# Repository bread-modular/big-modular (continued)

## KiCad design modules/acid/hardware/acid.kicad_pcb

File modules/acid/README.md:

# ACID: MIDI oscillator + envelope + vactrol SVF (10HP)

Bread Modular **MCO** + **ENV** (one ATtiny1616) and **SVF** (two-vactrol state-variable
filter, LP / HP / BP outs) on one Eurorack module, at Bread Modular's 3.3 V signal level. Each
output is one TL072 stage with a gain solder jumper on the back: x3 (shipped, the LOW level),
x3.9, or x11.1 (the user's BM DRIVE at 75 %).

| Panel (top to bottom) | Circuit |
|---|---|
| **MIDI** in, **AUDIO** in, **CV** in (top row) | MIDI: 8bit / LOW NPN front end, JP1 protected/direct jumper. Bypasses: AUDIO 10 Vpp -> 0..3.3 V (clips), unpatched = MCO; CV 0..5 V -> 0..3.3 V, unpatched = envelope |
| **DETUNE**, **MIX** | BM MCO knobs |
| **ATTACK**, **RELEASE** | BM ENV time knobs (attack = hold in HR mode), 4 mm lower than DETUNE / MIX |
| **HR / AR / ASR** LEDs, **MODE** button | Envelope model select (BM ENV algorithms) |
| **REC** button + LED (LED right of the button) | Records the envelope knob positions |
| **FREQ** | BM SVF cutoff/CV amount |
| **RES**, **CURVE** | BM SVF resonance (500k), freq curve (on the DETUNE/ATTACK and MIX/RELEASE columns) |
| **LP**, **HP**, **BP**, **ENV OUT** (bottom row) | Gain jumper JP2 / JP3 / JP4 on the back: open x3.0 (shipped), `M` x3.9, `H` x11.1; ~10 Vpp ceiling (TL072 clip), 500R. ENV OUT: envelope 0..3.3 V -> 0..5 V (protected) |

**Status: S3 schematic (gain jumpers; every net wired, ERC 0) + P4/R3 10HP re-layout (2026-11-06),
manual divide-and-conquer routing, 4-layer (every net routed; DRC 0 + 22 user-approved
vactrol-under-pot exclusions, 0 unconnected, parity 0); 10HP panel. JLCPCB export in
[`jlcpcb/`](jlcpcb/README.md): S3/R3 10HP set (2026-11-06), not supplier-accepted.
Not built.**

```sh
python3 -B tools/import_footprints.py   # one-time library import (pcbnew)
python3 -B tools/build_schematic.py     # schematic (placement by hand, wires by its router)
python3 -B tools/build_layout.py --panel-only   # regenerate the passive panel only; the routed carrier is the native source
kicad-cli pcb drc --format json --units mm --severity-all --schematic-parity \
   -o research/drc/vactrols.json hardware/acid.kicad_pcb
python3 -B tools/vactrol_exclusions.py research/drc/vactrols.json   # after every build_layout run
python3 -B tools/sim_level.py           # output-level model (research.md 3.4)
(cd ../.. && python3 -B opt/kicad-tools/kicad_tools.py check --config modules/acid/tools/kicad-project.json \
   --reports modules/acid/research/check-NEW)
```

Read [`Code.md`](Code.md) before changing hardware.

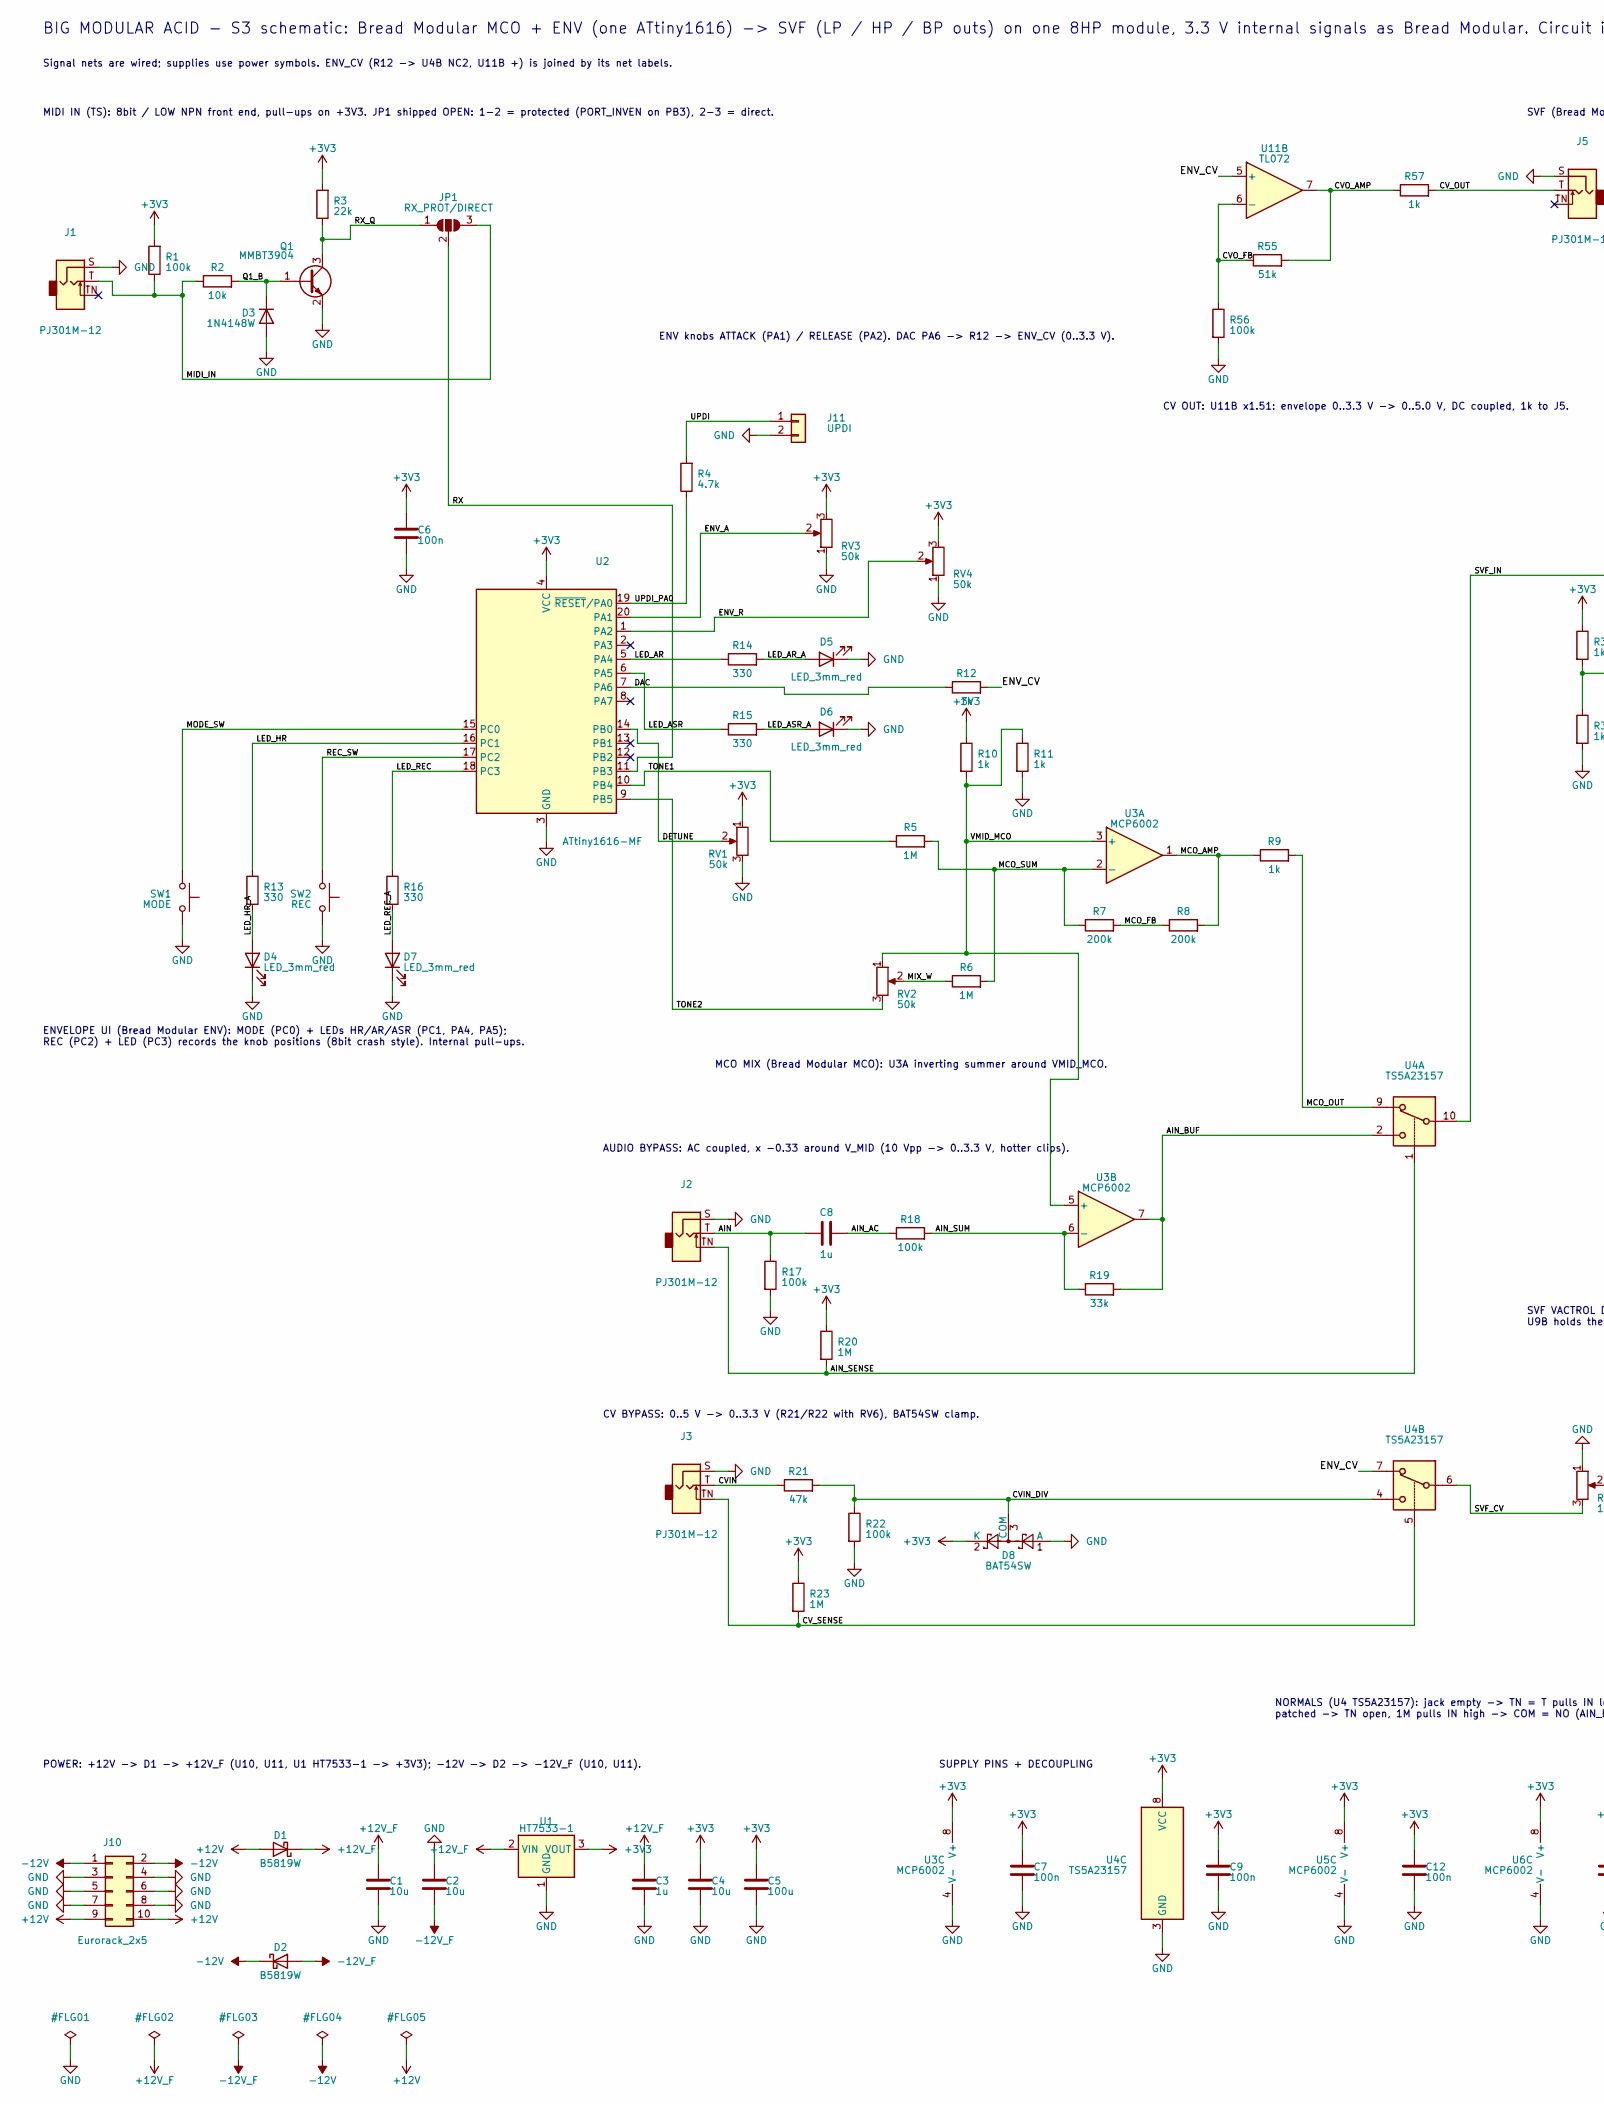
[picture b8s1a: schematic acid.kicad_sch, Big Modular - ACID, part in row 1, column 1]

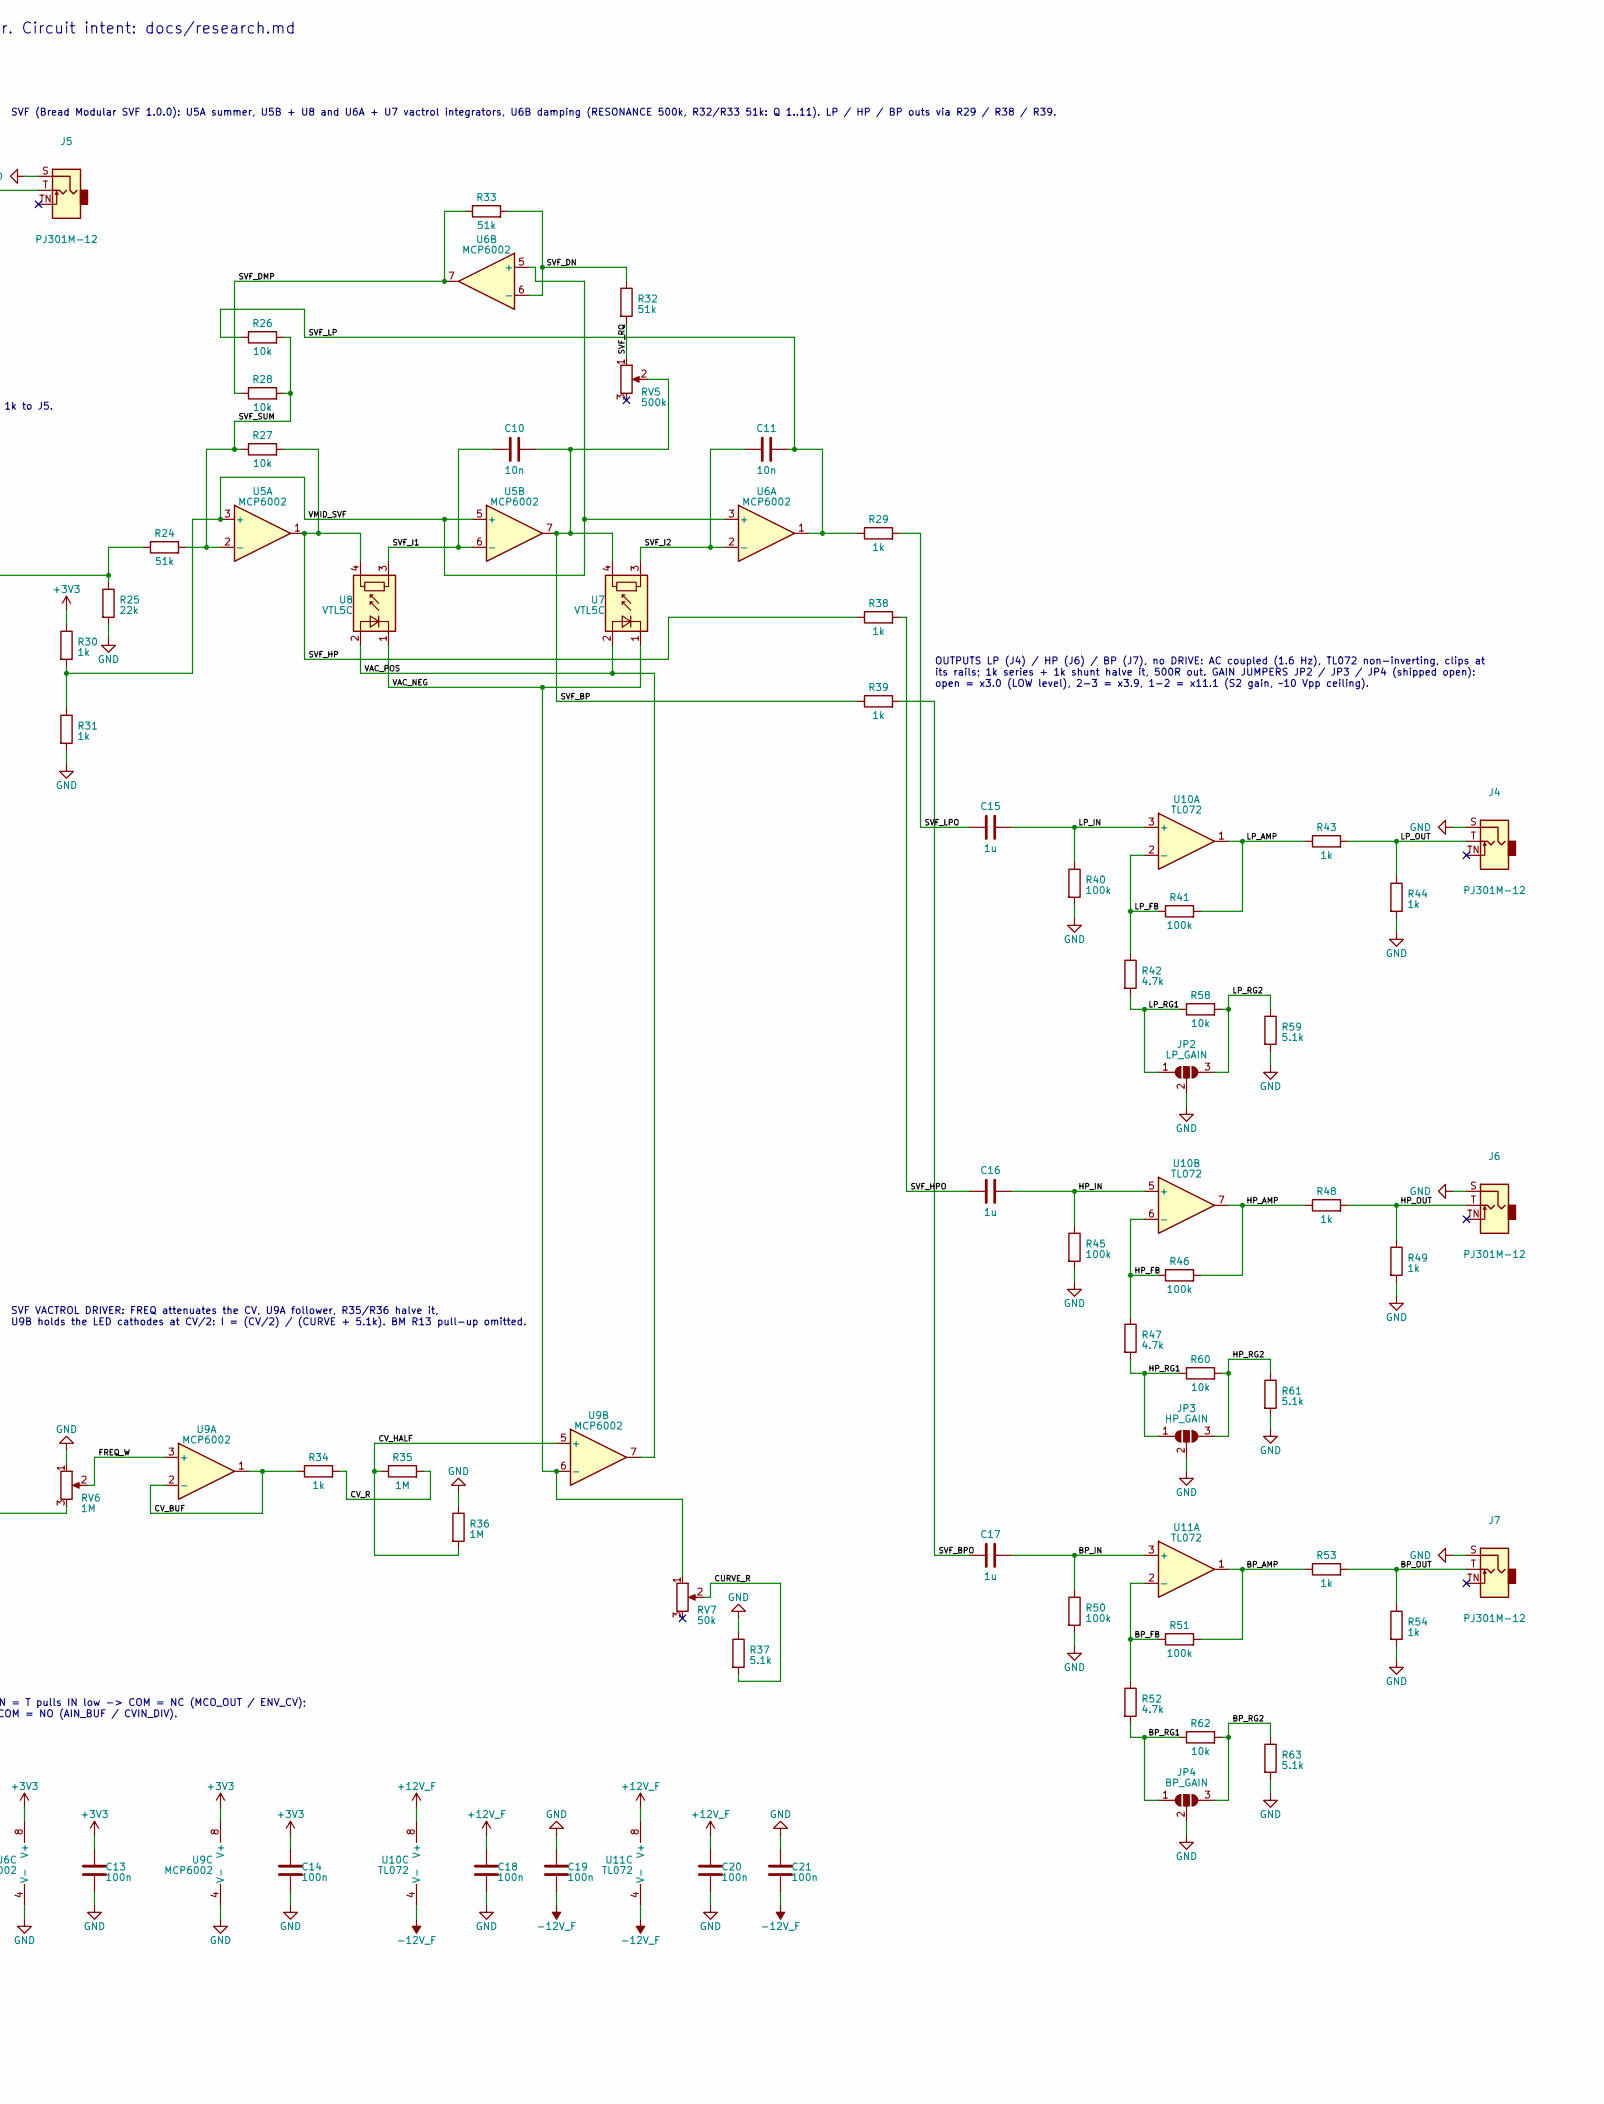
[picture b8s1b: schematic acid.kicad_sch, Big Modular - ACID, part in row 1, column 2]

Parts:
C1, C2, C4: 10u; C_0805_2012Metric; Voltage 25V; MPN CL21A106KAYNNNE; LCSC C15850
C3, C8: 1u; C_0805_2012Metric; Voltage 50V; MPN CL21B105KBFNNNE; LCSC C28323
C5: 100u; C_1206_3216Metric; Voltage 6.3V; MPN CL31A107MQHNNNE; LCSC C15008
C6, C7, C9, C12, C13, C14, C18, C19, C20, C21: 100n; C_0603_1608Metric; Voltage 50V; MPN CC0603KRX7R9BB104; LCSC C14663
C10, C11: 10n; C_0603_1608Metric; Voltage 50V; MPN 0603B103K500NT; LCSC C57112
C15, C16, C17: 1u; C_0805_2012Metric; Voltage 25V; MPN CL21B105KBFNNNE; LCSC C28323
D1, D2: B5819W; D_SOD-123; MPN B5819W SL; LCSC C8598
D3: 1N4148W; D_SOD-123; MPN 1N4148W; LCSC C81598
D4, D5, D6, D7: LED_3mm_red; LED_D3.0mm
D8: BAT54SW; SOT-323_SC-70; MPN BAT54SWT1G; LCSC C78260
J1, J2, J3, J4, J5, J6, J7: PJ301M-12; Jack_3.5mm_QingPu_WQP-PJ301M-12_Vertical
J10: Eurorack_2x5; PinHeader_2x05_P2.54mm_Vertical
J11: UPDI; PinHeader_1x02_P2.54mm_Vertical
JP1: RX_PROT/DIRECT; SolderJumper-3_P1.3mm_Open_RoundedPad1.0x1.5mm
JP2: LP_GAIN; SolderJumper-3_P1.3mm_Open_RoundedPad1.0x1.5mm
JP3: HP_GAIN; SolderJumper-3_P1.3mm_Open_RoundedPad1.0x1.5mm
JP4: BP_GAIN; SolderJumper-3_P1.3mm_Open_RoundedPad1.0x1.5mm
Q1: MMBT3904; SOT-23; MPN MMBT3904(RANGE:100-300); LCSC C20526
R1, R17, R18, R22, R40, R41, R45, R46, R50, R51, R56: 100k; R_0603_1608Metric; MPN 0603WAF1003T5E; LCSC C25803
R2, R26, R27, R28, R58, R60, R62: 10k; R_0603_1608Metric; MPN 0603WAF1002T5E; LCSC C25804
R3, R25: 22k; R_0603_1608Metric; MPN 0603WAF2202T5E; LCSC C31850
R4, R42, R47, R52: 4.7k; R_0603_1608Metric; MPN 0603WAF4701T5E; LCSC C23162
R5, R6, R20, R23, R35, R36: 1M; R_0603_1608Metric; MPN 0603WAF1004T5E; LCSC C22935
R7, R8: 200k; R_0603_1608Metric; MPN 0603WAF2003T5E; LCSC C25811
R9, R10, R11, R12, R29, R30, R31, R34, R38, R39: 1k; R_0603_1608Metric; MPN 0603WAF1001T5E; LCSC C21190
R13, R14, R15, R16: 330; R_0603_1608Metric; MPN 0603WAF3300T5E; LCSC C23138
R19: 33k; R_0603_1608Metric; MPN 0603WAF3302T5E; LCSC C4216
R21: 47k; R_0603_1608Metric; MPN 0603WAF4702T5E; LCSC C25819
R24, R32, R33, R55: 51k; R_0603_1608Metric; MPN 0603WAF5102T5E; LCSC C23196
R37, R59, R61, R63: 5.1k; R_0603_1608Metric; MPN 0603WAF5101T5E; LCSC C23186
R43, R44, R48, R49, R53, R54, R57: 1k; R_1206_3216Metric; MPN ESR18EZPF1001; LCSC C2074262
RV1, RV2, RV3, RV4, RV7: 50k; Potentiometer_RV09
RV5: 500k; Potentiometer_RV09
RV6: 1M; Potentiometer_RV09
SW1: MODE; SW_PUSH_6mm_H7.3mm; MPN 6x6x7 mm THT tact switch, 4 pins (gener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
SW2: REC; SW_PUSH_6mm_H7.3mm; MPN 6x6x7 mm THT tact switch, 4 pins (gener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
U1: HT7533-1; SOT-89-3; MPN HT7533-1; LCSC C14289
U2: ATtiny1616-MF; VQFN-20-1EP_3x3mm_P0.4mm_EP1.7x1.7mm; MPN ATTINY1616-MF; LCSC C5227638
U3, U5, U6, U9: MCP6002; SOIC-8_3.9x4.9mm_P1.27mm; MPN MCP6002T-I/SN; LCSC C7377
U4: TS5A23157; TSSOP-10_3x3mm_P0.5mm; MPN TS5A23157DGSR; LCSC C11133
U7, U8: VTL5C
U10, U11: TL072; SOIC-8_3.9x4.9mm_P1.27mm; MPN TL072CDT; LCSC C6961

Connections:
+3V3: C4.1, C5.1, C6.1, C7.1, C9.1, C12.1, C13.1, C14.1, D8.2 (K), R1.2, R3.2, R10.1, R20.1, R23.1, R30.1, RV1.1, RV3.3, RV4.3, U1.3 (VOUT), U2.4 (VCC), U3.8 (V+), U4.8 (VCC), U5.8 (V+), U6.8 (V+), U9.8 (V+)
+12V: D1.2 (A), J10.9, J10.10
+12V_F: C1.1, C3.1, C18.1, C20.1, D1.1 (K), U1.2 (VIN), U10.8 (V+), U11.8 (V+)
-12V: D2.1 (K), J10.1, J10.2
-12V_F: C2.2, C19.2, C21.2, D2.2 (A), U10.4 (V-), U11.4 (V-)
/AIN: C8.1, J2.T, R17.1
/AIN_AC: C8.2, R18.1
/AIN_BUF: R19.2, U3.7, U4.2
/AIN_SENSE: J2.TN, R20.2, U4.1
/AIN_SUM: R18.2, R19.1, U3.6 (-)
/BP_AMP: R51.2, R53.1, U11.1
/BP_FB: R51.1, R52.1, U11.2 (-)
/BP_IN: C17.2, R50.1, U11.3 (+)
/BP_OUT: J7.T, R53.2, R54.1
/BP_RG1: JP4.1 (A), R52.2, R62.1
/BP_RG2: JP4.3 (B), R62.2, R63.1
/CURVE_R: R37.2, RV7.2
/CVIN: J3.T, R21.1
/CVIN_DIV: D8.3 (COM), R21.2, R22.1, U4.4
/CVO_AMP: R55.2, R57.1, U11.7
/CVO_FB: R55.1, R56.1, U11.6 (-)
/CV_BUF: R34.1, U9.1, U9.2 (-)
/CV_HALF: R35.1, R36.2, U9.5 (+)
/CV_OUT: J5.T, R57.2
/CV_R: R34.2, R35.2
/CV_SENSE: J3.TN, R23.2, U4.5
/DAC: R12.1, U2.7 (PA6)
/DETUNE: RV1.2, U2.14 (PB0)
/ENV_A: RV3.2, U2.20 (PA1)
/ENV_CV: R12.2, U4.7, U11.5 (+)
/ENV_R: RV4.2, U2.1 (PA2)
/FREQ_W: RV6.2, U9.3 (+)
/HP_AMP: R46.2, R48.1, U10.7
/HP_FB: R46.1, R47.1, U10.6 (-)
/HP_IN: C16.2, R45.1, U10.5 (+)
/HP_OUT: J6.T, R48.2, R49.1
/HP_RG1: JP3.1 (A), R47.2, R60.1
/HP_RG2: JP3.3 (B), R60.2, R61.1
/LED_AR: R14.1, U2.5 (PA4)
/LED_AR_A: D5.2 (A), R14.2
/LED_ASR: R15.1, U2.6 (PA5)
/LED_ASR_A: D6.2 (A), R15.2
/LED_HR: R13.1, U2.16 (PC1)
/LED_HR_A: D4.2 (A), R13.2
/LED_REC: R16.1, U2.18 (PC3)
/LED_REC_A: D7.2 (A), R16.2
/LP_AMP: R41.2, R43.1, U10.1
/LP_FB: R41.1, R42.1, U10.2 (-)
/LP_IN: C15.2, R40.1, U10.3 (+)
/LP_OUT: J4.T, R43.2, R44.1
/LP_RG1: JP2.1 (A), R42.2, R58.1
/LP_RG2: JP2.3 (B), R58.2, R59.1
/MCO_AMP: R8.2, R9.1, U3.1
/MCO_FB: R7.2, R8.1
/MCO_OUT: R9.2, U4.9
/MCO_SUM: R5.2, R6.2, R7.1, U3.2 (-)
/MIDI_IN: J1.T, JP1.3 (B), R1.1, R2.1
/MIX_W: R6.1, RV2.2
/MODE_SW: SW1.1, U2.15 (PC0)
/Q1_B: D3.1 (K), Q1.1 (B), R2.2
/REC_SW: SW2.1, U2.17 (PC2)
/RX: JP1.2 (C), U2.11 (PB3)
/RX_Q: JP1.1 (A), Q1.3 (C), R3.1
/SVF_BP: C10.2, R39.1, RV5.2, U5.7, U7.4
/SVF_BPO: C17.1, R39.2
/SVF_CV: RV6.3, U4.6
/SVF_DMP: R28.1, R33.1, U6.7
/SVF_DN: R32.1, R33.2, U6.6 (-)
/SVF_HP: R27.2, R38.1, U5.1, U8.4
/SVF_HPO: C16.1, R38.2
/SVF_I1: C10.1, U5.6 (-), U8.3
/SVF_I2: C11.1, U6.2 (-), U7.3
/SVF_IN: R24.1, R25.1, U4.10
/SVF_LP: C11.2, R26.1, R29.1, U6.1
/SVF_LPO: C15.1, R29.2
/SVF_RQ: R32.2, RV5.1
/SVF_SUM: R24.2, R26.2, R27.1, R28.2, U5.2 (-)
/TONE1: R5.1, U2.10 (PB4)
/TONE2: RV2.3, U2.9 (PB5)
/UPDI: J11.1, R4.2
/UPDI_PA0: R4.1, U2.19 (~RESET/PA0)
/VAC_NEG: RV7.1, U7.1 (-), U8.1 (-), U9.6 (-)
/VAC_POS: U7.2 (+), U8.2 (+), U9.7
/VMID_MCO: R10.2, R11.1, RV2.1, U3.3 (+), U3.5 (+)
/VMID_SVF: R30.2, R31.1, U5.3 (+), U5.5 (+), U6.3 (+), U6.5 (+)
GND: C1.2, C2.1, C3.2, C4.2, C5.2, C6.2, C7.2, C9.2, C12.2, C13.2, C14.2, C18.2, C19.1, C20.2, C21.1, D3.2 (A), D4.1 (K), D5.1 (K), D6.1 (K), D7.1 (K), D8.1 (A), J1.S, J2.S, J3.S, J4.S, J5.S, J6.S, J7.S, J10.3, J10.4, J10.5, J10.6, J10.7, J10.8, J11.2, JP2.2 (C), JP3.2 (C), JP4.2 (C), Q1.2 (E), R11.2, R17.2, R22.2, R25.2, R31.2, R36.1, R37.1, R40.2, R44.2, R45.2, R49.2, R50.2, R54.2, R56.2, R59.2, R61.2, R63.2, RV1.3, RV3.1, RV4.1, RV6.1, SW1.2, SW2.2, U1.1 (GND), U2.3 (GND), U2.21 (GND), U3.4 (V-), U4.3 (GND), U5.4 (V-), U6.4 (V-), U9.4 (V-)

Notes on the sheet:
BIG MODULAR ACID - S3 schematic: Bread Modular MCO + ENV (one ATtiny1616) -> SVF (LP / HP / BP outs) on one 8HP module, 3.3 V internal signals as Bread Modular. Circuit intent: docs/research.md
SVF (Bread Modular SVF 1.0.0): U5A summer, U5B + U8 and U6A + U7 vactrol integrators, U6B damping (RESONANCE 500k, R32/R33 51k: Q 1..11). LP / HP / BP outs via R29 / R38 / R39.
SUPPLY PINS + DECOUPLING
Signal nets are wired; supplies use power symbols. ENV_CV (R12 -> U4B NC2, U11B +) is joined by its net labels.
MIDI IN (TS): 8bit / LOW NPN front end, pull-ups on +3V3. JP1 shipped OPEN: 1-2 = protected (PORT_INVEN on PB3), 2-3 = direct.
POWER: +12V -> D1 -> +12V_F (U10, U11, U1 HT7533-1 -> +3V3); -12V -> D2 -> -12V_F (U10, U11).
SVF VACTROL DRIVER: FREQ attenuates the CV, U9A follower, R35/R36 halve it, U9B holds the LED cathodes at CV/2: I = (CV/2) / (CURVE + 5.1k). BM R13 pull-up omitted.
ENV knobs ATTACK (PA1) / RELEASE (PA2). DAC PA6 -> R12 -> ENV_CV (0..3.3 V).
ENVELOPE UI (Bread Modular ENV): MODE (PC0) + LEDs HR/AR/ASR (PC1, PA4, PA5); REC (PC2) + LED (PC3) records the knob positions (8bit crash style). Internal pull-ups.
NORMALS (U4 TS5A23157): jack empty -> TN = T pulls IN low -> COM = NC (MCO_OUT / ENV_CV); patched -> TN open, 1M pulls IN high -> COM = NO (AIN_BUF / CVIN_DIV).
CV BYPASS: 0..5 V -> 0..3.3 V (R21/R22 with RV6), BAT54SW clamp.
OUTPUTS LP (J4) / HP (J6) / BP (J7), no DRIVE: AC coupled (1.6 Hz), TL072 non-inverting, clips at its rails; 1k series + 1k shunt halve it, 500R out. GAIN JUMPERS JP2 / JP3 / JP4 (shipped open): open = x3.0 (LOW level), 2-3 = x3.9, 1-2 = x11.1 (S2 gain, ~10 Vpp ceiling).
MCO MIX (Bread Modular MCO): U3A inverting summer around VMID_MCO.
AUDIO BYPASS: AC coupled, x -0.33 around V_MID (10 Vpp -> 0..3.3 V, hotter clips).
CV OUT: U11B x1.51: envelope 0..3.3 V -> 0..5.0 V, DC coupled, 1k to J5.

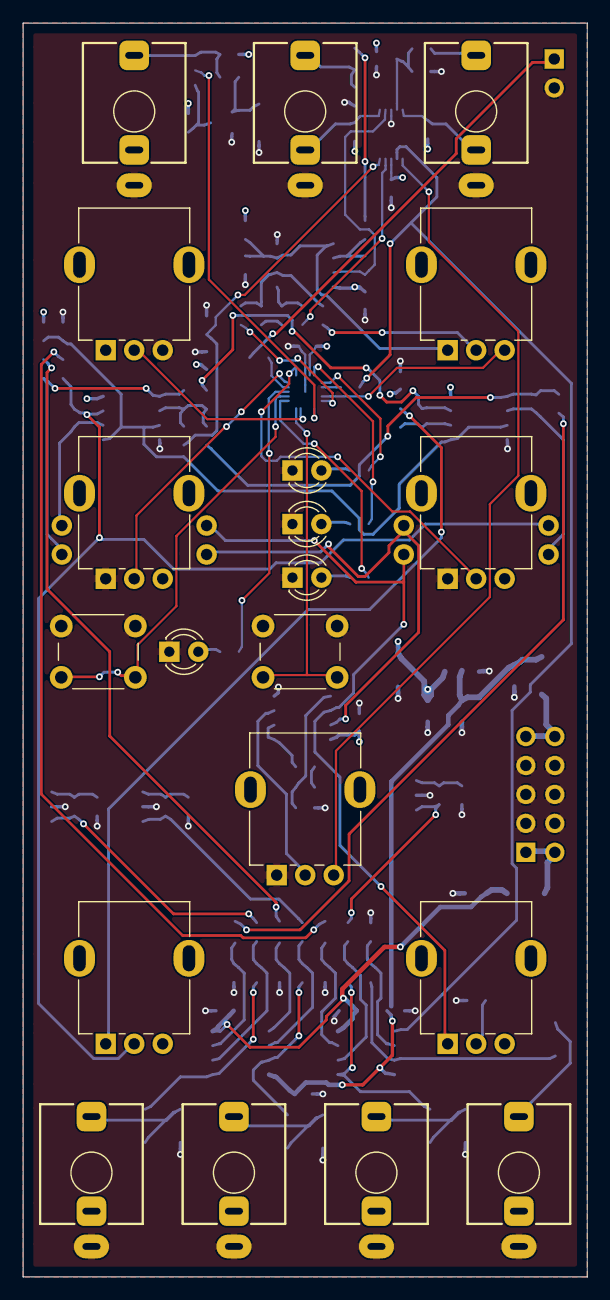
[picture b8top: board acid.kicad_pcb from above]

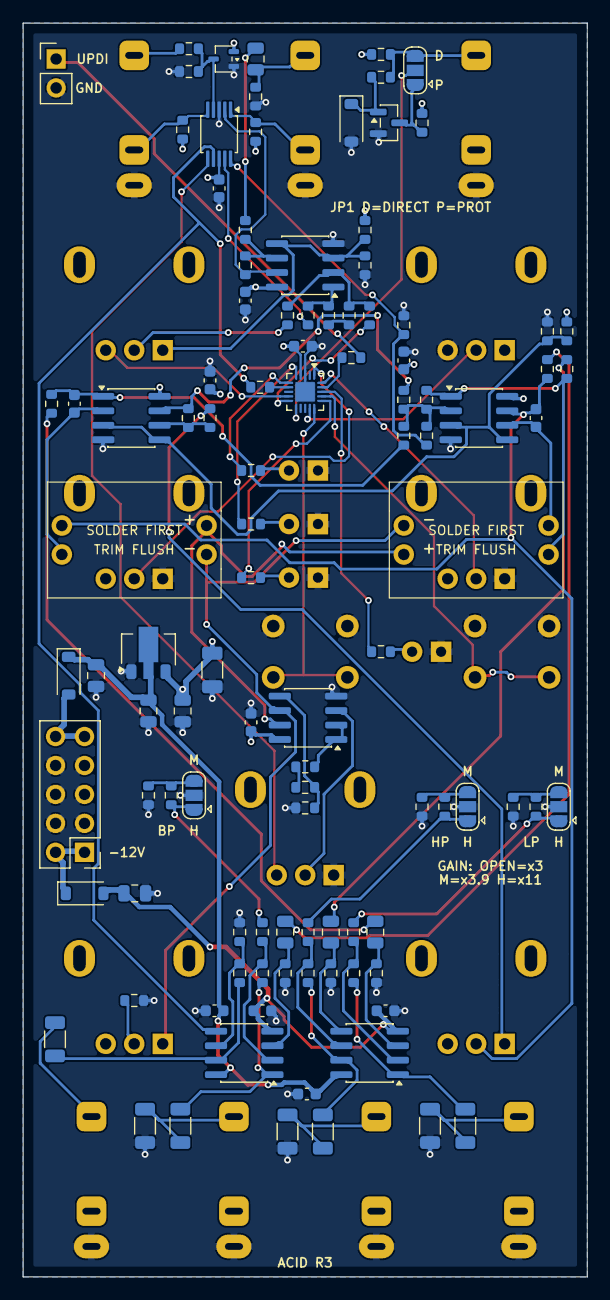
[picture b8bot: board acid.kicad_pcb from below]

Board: 4 copper layers, 49.5 x 110.0 mm, 126 parts (106 on the bottom side), 86 nets.

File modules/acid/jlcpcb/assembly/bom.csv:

Comment,Designator,Footprint,LCSC Part #,Quantity,Manufacturer,MPN
10u,"C1, C2, C4",C_0805_2012Metric,C15850,3,Samsung,CL21A106KAYNNNE
1u,"C3, C8, C15, C16, C17",C_0805_2012Metric,C28323,5,Samsung,CL21B105KBFNNNE
100u,C5,C_1206_3216Metric,C15008,1,Samsung,CL31A107MQHNNNE
100n,"C6, C7, C9, C12, C13, C14, C18, C19, C20, C21",C_0603_1608Metric,C14663,10,YAGEO,CC0603KRX7R9BB104
10n,"C10, C11",C_0603_1608Metric,C57112,2,FH (Guangdong Fenghua),0603B103K500NT
B5819W,"D1, D2",D_SOD-123,C8598,2,CJ (Jiangsu Changjing),B5819W SL
1N4148W,D3,D_SOD-123,C81598,1,ST(Semtech),1N4148W
BAT54SW,D8,SOT-323_SC-70,C78260,1,onsemi,BAT54SWT1G
MMBT3904,Q1,SOT-23,C20526,1,CJ (Jiangsu Changjing),MMBT3904(RANGE:100-300)
100k,"R1, R17, R18, R22, R40, R41, R45, R46, R50, R51, R56",R_0603_1608Metric,C25803,11,UNI-ROYAL,0603WAF1003T5E
10k,"R2, R26, R27, R28",R_0603_1608Metric,C25804,4,UNI-ROYAL,0603WAF1002T5E
22k,"R3, R25",R_0603_1608Metric,C31850,2,UNI-ROYAL,0603WAF2202T5E
4.7k,"R4, R42, R47, R52",R_0603_1608Metric,C23162,4,UNI-ROYAL,0603WAF4701T5E
1M,"R5, R6, R20, R23, R35, R36",R_0603_1608Metric,C22935,6,UNI-ROYAL,0603WAF1004T5E
200k,"R7, R8",R_0603_1608Metric,C25811,2,UNI-ROYAL,0603WAF2003T5E
1k,"R9, R10, R11, R12, R29, R30, R31, R34, R38, R39",R_0603_1608Metric,C21190,10,UNI-ROYAL,0603WAF1001T5E
330,"R13, R14, R15, R16",R_0603_1608Metric,C23138,4,UNI-ROYAL,0603WAF3300T5E
33k,R19,R_0603_1608Metric,C4216,1,UNI-ROYAL,0603WAF3302T5E
47k,R21,R_0603_1608Metric,C25819,1,UNI-ROYAL,0603WAF4702T5E
51k,"R24, R32, R33, R55",R_0603_1608Metric,C23196,4,UNI-ROYAL,0603WAF5102T5E
5.1k,R37,R_0603_1608Metric,C23186,1,UNI-ROYAL,0603WAF5101T5E
1k,"R43, R44, R48, R49, R53, R54, R57",R_1206_3216Metric,C2074262,7,ROHM,ESR18EZPF1001
HT7533-1,U1,SOT-89-3,C14289,1,Holtek,HT7533-1
ATtiny1616-MNR,U2,VQFN-20-1EP_3x3mm_P0.4mm_EP1.7x1.7mm,C507118,1,Microchip,ATTINY1616-MNR
MCP6002,"U3, U5, U6, U9",SOIC-8_3.9x4.9mm_P1.27mm,C7377,4,Microchip,MCP6002T-I/SN
TS5A23157,U4,TSSOP-10_3x3mm_P0.5mm,C11133,1,Texas Instruments,TS5A23157DGSR
TL072,"U10, U11",SOIC-8_3.9x4.9mm_P1.27mm,C6961,2,STMicroelectronics,TL072CDT
